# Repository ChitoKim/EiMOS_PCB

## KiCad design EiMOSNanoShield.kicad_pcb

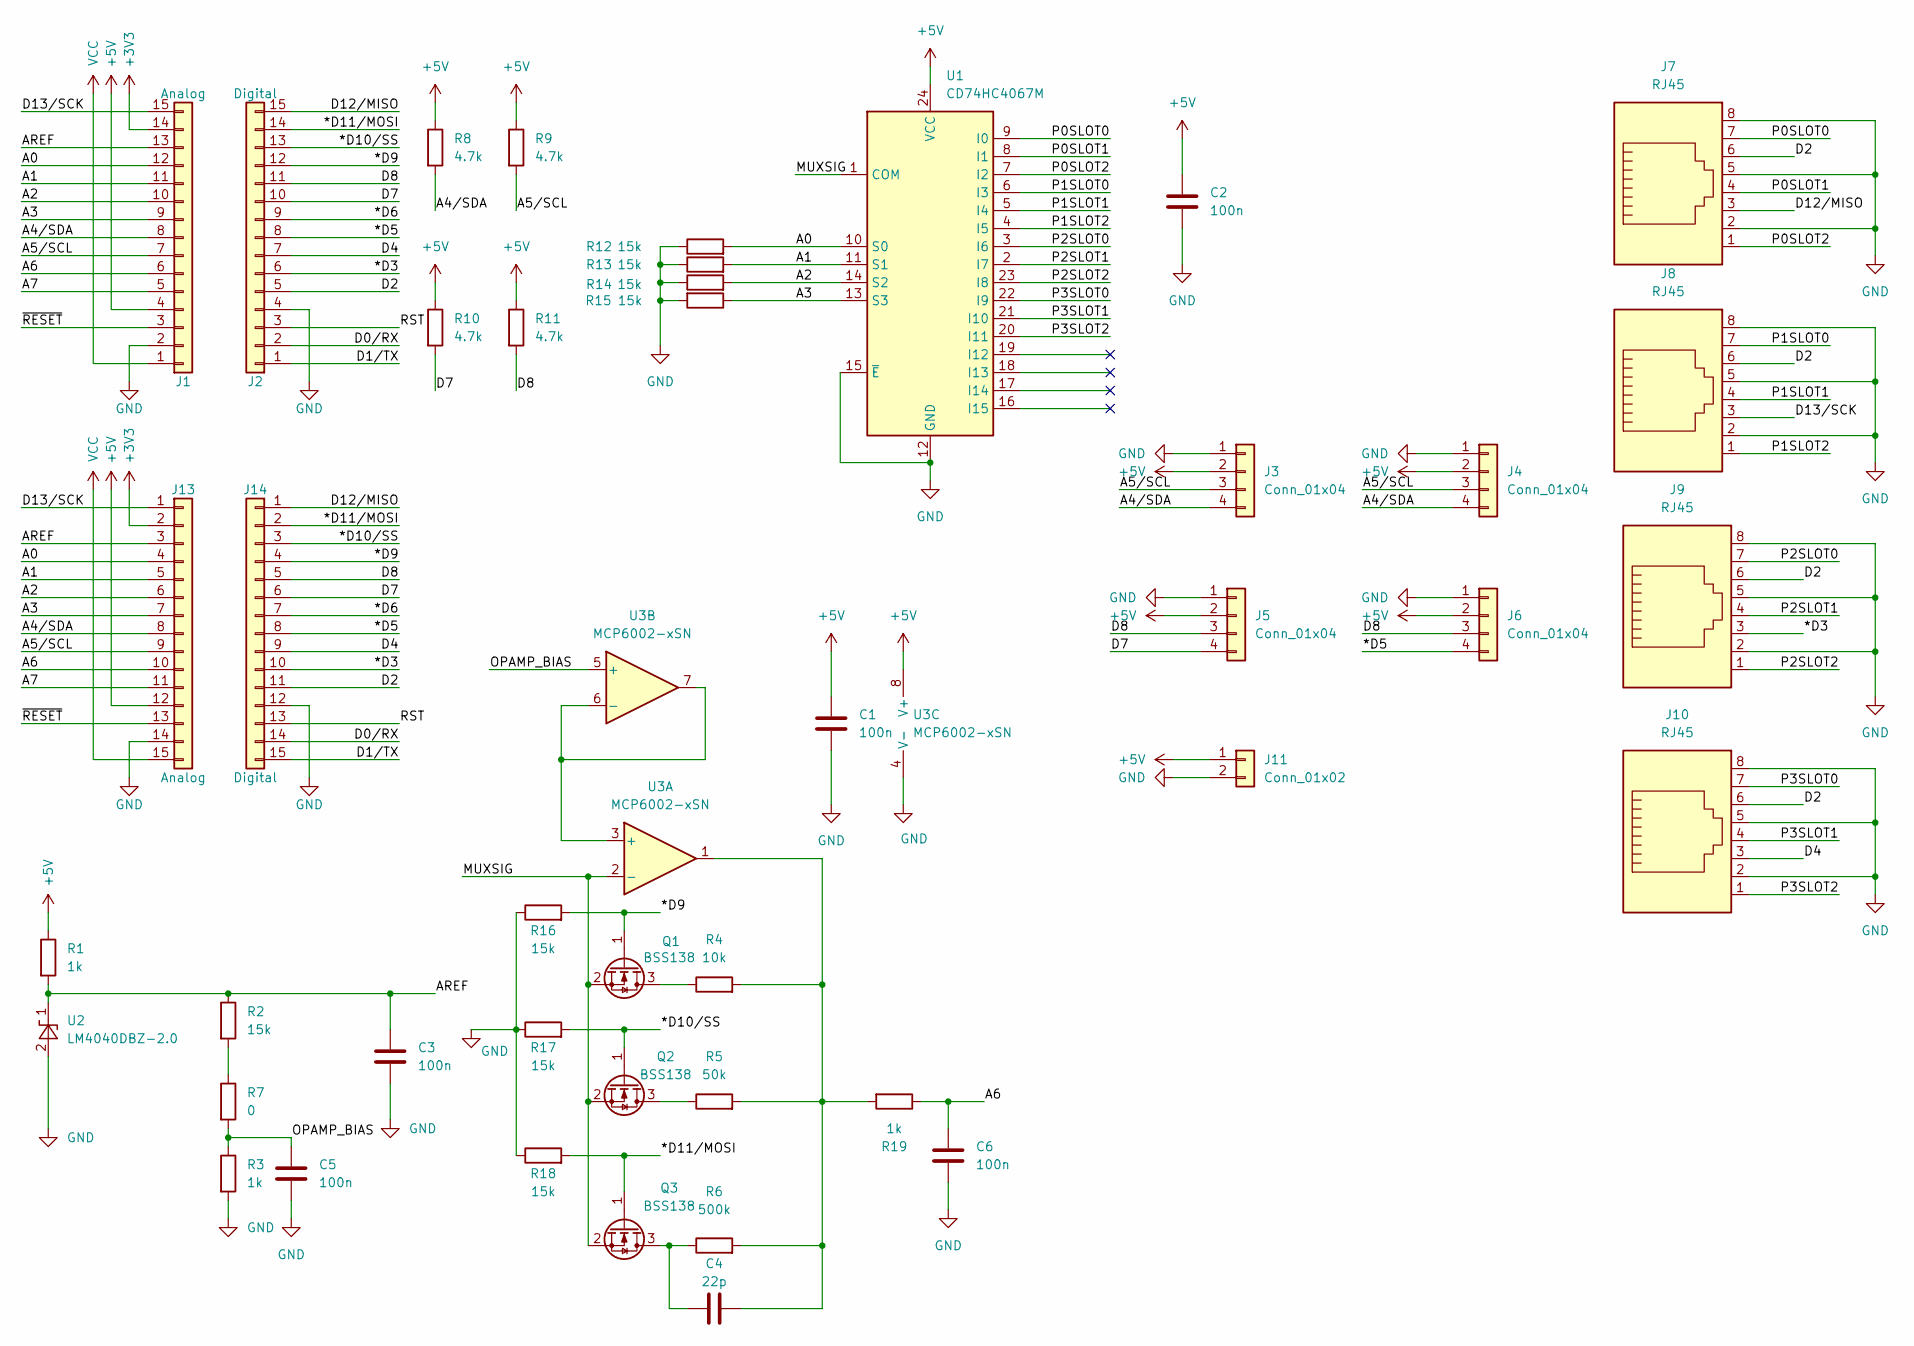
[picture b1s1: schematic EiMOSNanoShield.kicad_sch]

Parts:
C1, C2, C3, C5, C6: 100n; C_0805_2012Metric
C4: 22p; C_0805_2012Metric
J1: Analog; PinSocket_1x15_P2.54mm_Vertical
J2: Digital; PinSocket_1x15_P2.54mm_Vertical
J3, J4, J5, J6: Conn_01x04; JST_XH_B4B-XH-A_1x04_P2.50mm_Vertical
J7, J8, J9, J10: RJ45; RJ45_Amphenol_54602-x08_Horizontal
J11: Conn_01x02; PinHeader_1x02_P2.54mm_Vertical
J13: Analog; PinHeader_1x15_P2.54mm_Vertical
J14: Digital; PinHeader_1x15_P2.54mm_Vertical
Q1, Q2, Q3: BSS138; SOT-23
R1, R3, R19: 1k; R_0805_2012Metric
R2, R12, R13, R14, R15, R16, R17, R18: 15k; R_0805_2012Metric
R4: 10k; R_0805_2012Metric
R5: 50k; R_0805_2012Metric
R6: 500k; R_0805_2012Metric
R7: 0; R_0805_2012Metric
R8, R9, R10, R11: 4.7k; R_0805_2012Metric
U1: CD74HC4067M; SOIC-24W_7.5x15.4mm_P1.27mm
U2: LM4040DBZ-2.0; SOT-23
U3: MCP6002-xSN; SOIC-8_3.9x4.9mm_P1.27mm

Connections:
+3V3: J1.14, J13.2
+5V: C1.1, C2.1, J1.4, J3.2, J4.2, J5.2, J6.2, J11.1, J13.12, R1.1, R8.1, R9.1, R10.1, R11.1, U1.24 (VCC), U3.8 (V+)
/*D3: J2.6, J9.3, J14.10
/*D5: J2.8, J6.4, J14.8
/*D6: J2.9, J14.7
/*D9: J2.12, J14.4, Q1.1 (G), R16.2
/*D10/SS: J2.13, J14.3, Q2.1 (G), R17.2
/*D11/MOSI: J2.14, J14.2, Q3.1 (G), R18.2
/A0: J1.12, J13.4, R12.2, U1.10 (S0)
/A1: J1.11, J13.5, R13.2, U1.11 (S1)
/A2: J1.10, J13.6, R14.2, U1.14 (S2)
/A3: J1.9, J13.7, R15.1, U1.13 (S3)
/A4/SDA: J1.8, J3.4, J4.4, J13.8, R8.2
/A5/SCL: J1.7, J3.3, J4.3, J13.9, R9.2
/A6: C6.1, J1.6, J13.10, R19.1
/A7: J1.5, J13.11
/AREF: C3.1, J1.13, J13.3, R1.2, R2.1, U2.1 (K)
/D0/RX: J2.2, J14.14
/D1/TX: J2.1, J14.15
/D2: J2.5, J7.6, J8.6, J9.6, J10.6, J14.11
/D4: J2.7, J10.3, J14.9
/D7: J2.10, J5.4, J14.6, R10.2
/D8: J2.11, J5.3, J6.3, J14.5, R11.2
/D12/MISO: J2.15, J7.3, J14.1
/D13/SCK: J1.15, J8.3, J13.1
/MUXSIG: Q1.2 (S), Q2.2 (S), Q3.2 (S), U1.1 (COM), U3.2 (-)
/OPAMP_BIAS: C5.1, R3.1, R7.2, U3.5 (+)
/P0SLOT0: J7.7, U1.9 (I0)
/P0SLOT1: J7.4, U1.8 (I1)
/P0SLOT2: J7.1, U1.7 (I2)
/P1SLOT0: J8.7, U1.6 (I3)
/P1SLOT1: J8.4, U1.5 (I4)
/P1SLOT2: J8.1, U1.4 (I5)
/P2SLOT0: J9.7, U1.3 (I6)
/P2SLOT1: J9.4, U1.2 (I7)
/P2SLOT2: J9.1, U1.23 (I8)
/P3SLOT0: J10.7, U1.22 (I9)
/P3SLOT1: J10.4, U1.21 (I10)
/P3SLOT2: J10.1, U1.20 (I11)
/RST: J2.3, J14.13
/~RESET: J1.3, J13.13
GND: C1.2, C2.2, C3.2, C5.2, C6.2, J1.2, J2.4, J3.1, J4.1, J5.1, J6.1, J7.2, J7.5, J7.8, J8.2, J8.5, J8.8, J9.2, J9.5, J9.8, J10.2, J10.5, J10.8, J11.2, J13.14, J14.12, R3.2, R12.1, R13.1, R14.1, R15.2, R16.1, R17.1, R18.1, U1.12 (GND), U1.15 (~E), U2.2 (A), U3.4 (V-)
unnamed: C4.2, R4.2, R5.2, R6.2, R19.2, U3.1
unnamed: Q1.3 (D), R4.1
unnamed: Q2.3 (D), R5.1
unnamed: C4.1, Q3.3 (D), R6.1
unnamed: R2.2, R7.1
unnamed: U3.3 (+), U3.6 (-), U3.7
VCC: J1.1, J13.15

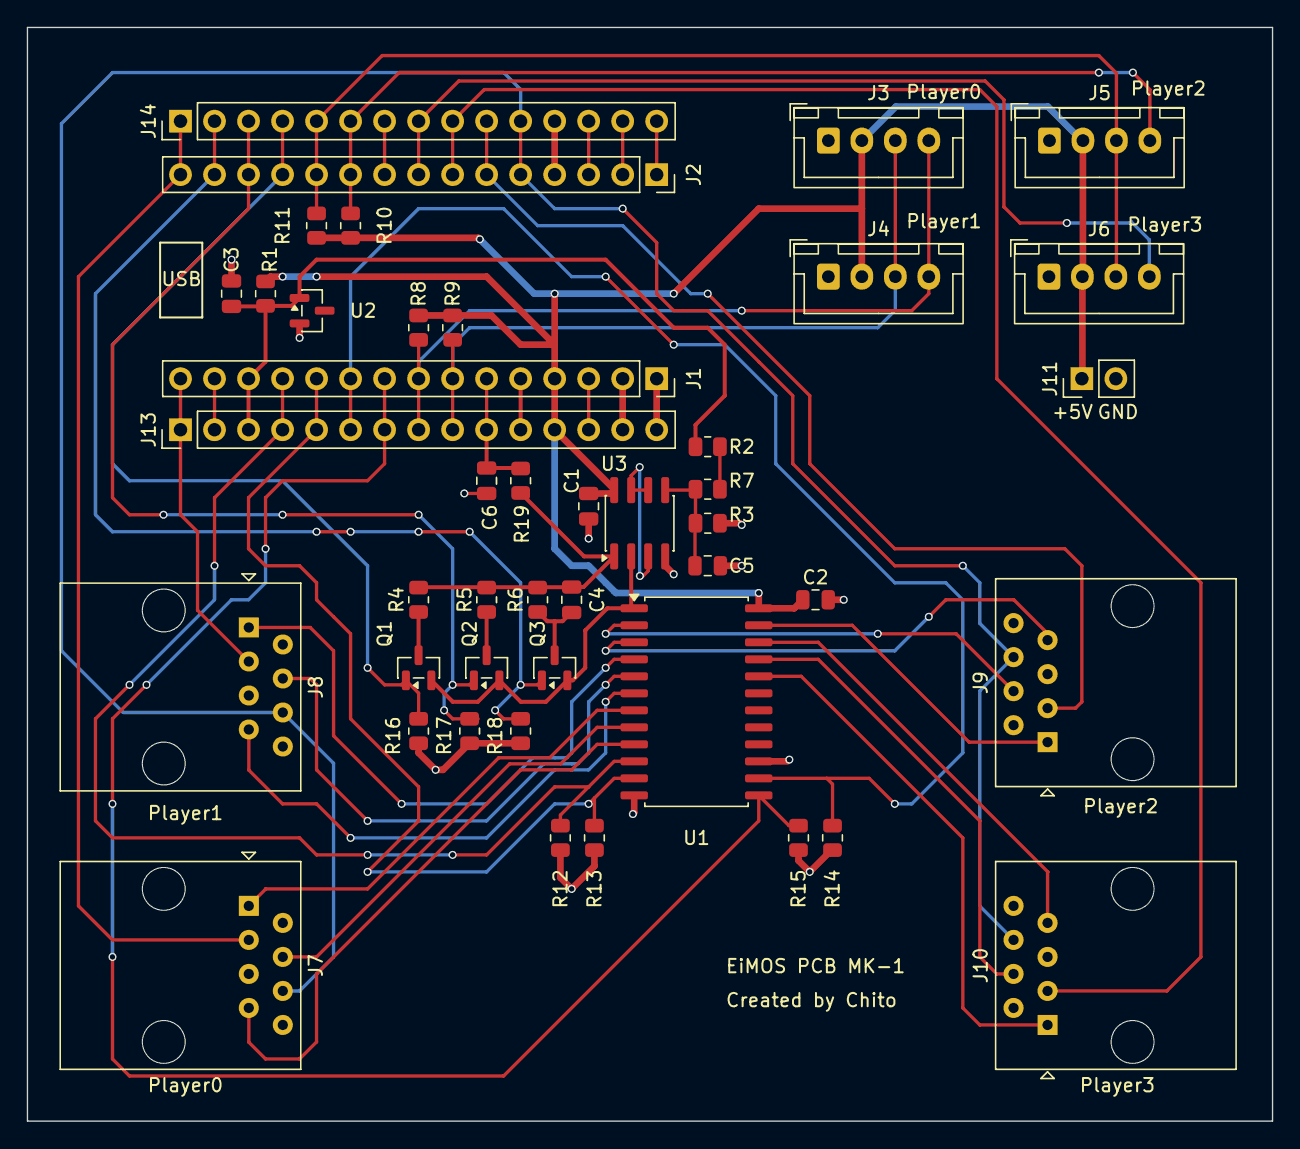
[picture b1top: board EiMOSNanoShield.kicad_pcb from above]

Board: 2 copper layers, 93.0 x 81.7 mm, 44 parts (0 on the bottom side), 49 nets.

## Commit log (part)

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2026-06-13 Added RC low pass filter before ADC, and also a test power pin header
